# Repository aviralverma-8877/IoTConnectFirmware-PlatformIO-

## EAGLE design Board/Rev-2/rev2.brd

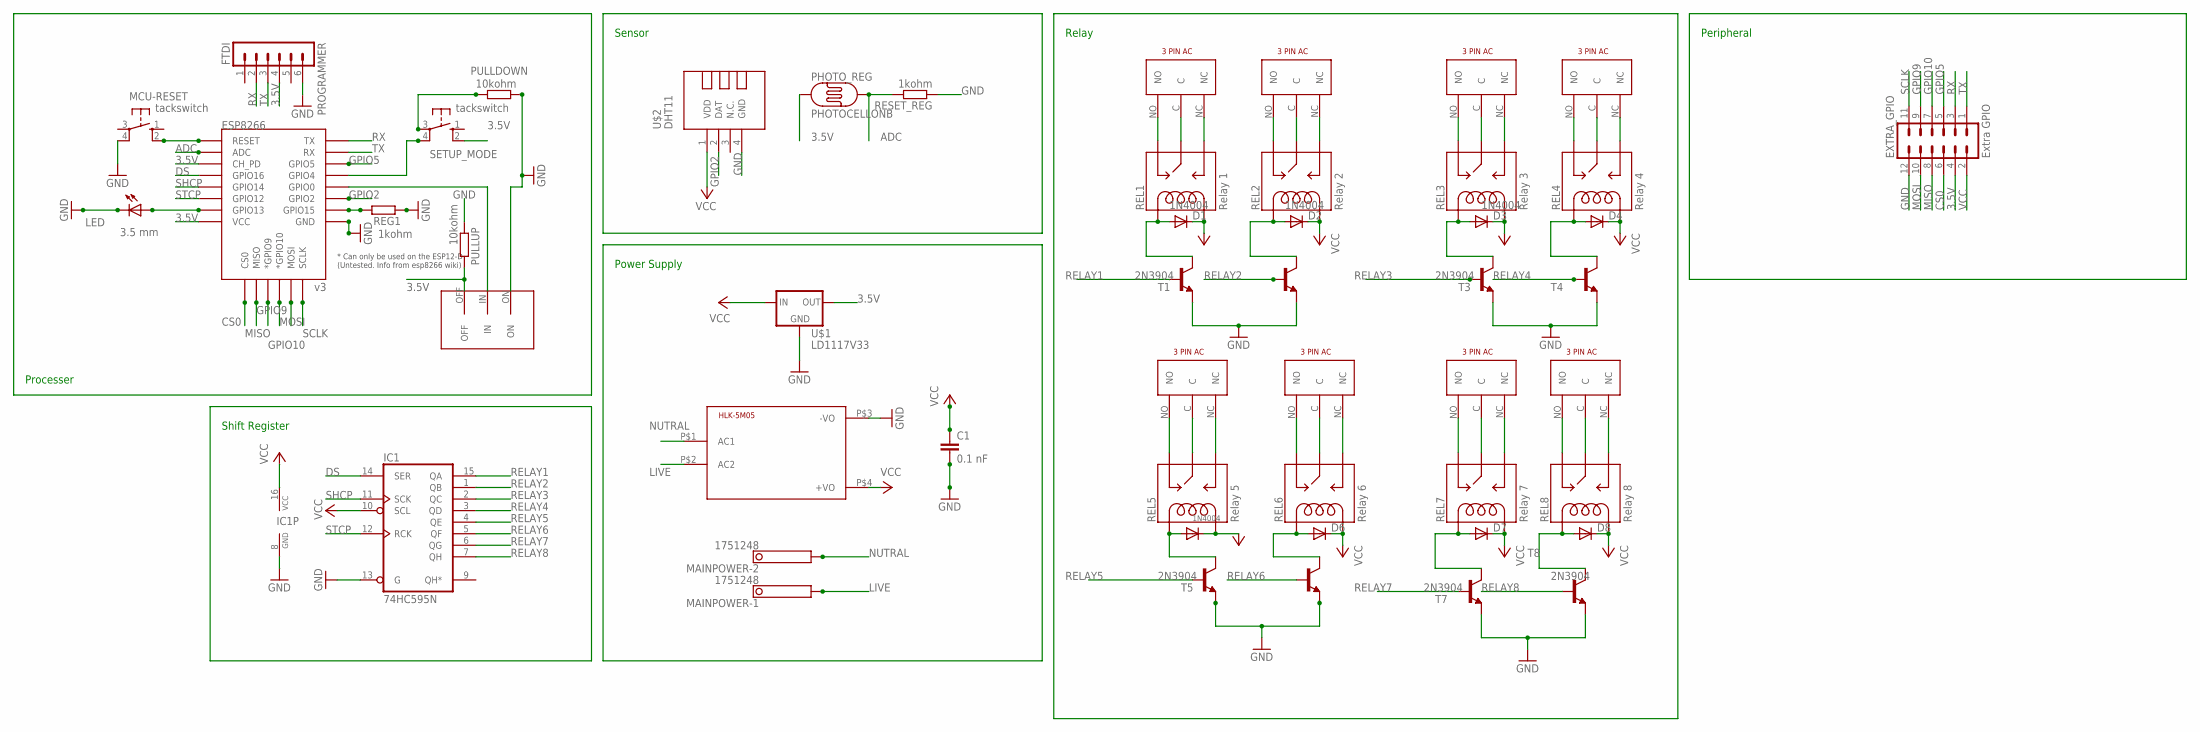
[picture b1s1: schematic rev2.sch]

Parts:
C1: 0.1 nF; CAP-PTH-SMALL-KIT
CON-REL-1, CON-REL-2, CON-REL-3, CON-REL-4, CON-REL-5, CON-REL-6, CON-REL-7, CON-REL-8: 3PINAC; LIB
D1, D2, D3, D4, D5, D6, D7, D8: 1N4004; DO41-10
ESP8266: v3; ESP12E-SMD
EXTRA_GPIO: Extra GPIO; MA06-2
FLASH: TOGGLE_SWITCH
HLK-5M05: AC to DC Converter; HKLPM01
IC1: 74HC595N; DIL16
LED: 3.5 mm; LED3MM
MAINPOWER: 1751248
MCU-RESET: tackswitch; B3F-10XX
PHOTO_REG: PHOTOCELLONB; ON_BOARD
PROGRAMMER: FTDI; MA06-1
PULLDOWN: 10kohm; 0204/7
PULLUP: 10kohm; 0204/7
REG1: 1kohm; 0204/7
REL1: Relay 1; SRD-05VDC-SL-C
REL2: Relay 2; SRD-05VDC-SL-C
REL3: Relay 3; SRD-05VDC-SL-C
REL4: Relay 4; SRD-05VDC-SL-C
REL5: Relay 5; SRD-05VDC-SL-C
REL6: Relay 6; SRD-05VDC-SL-C
REL7: Relay 7; SRD-05VDC-SL-C
REL8: Relay 8; SRD-05VDC-SL-C
RESET_REG: 1kohm; 0204/7
SETUP_MODE: tackswitch; B3F-10XX
T1, T2, T3, T4, T5, T6, T7, T8: 2N3904; TO92-EBC
U$1: LD1117V33
U$2: DHT11; TEMP-HUM-SENSOR-DHT11

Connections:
3.5V: ESP8266.CH_PD, ESP8266.VCC, EXTRA_GPIO.4, FLASH.OFF, PHOTO_REG.1, PROGRAMMER.4, PULLUP.2, SETUP_MODE.2 (S1), U$1.OUT
ADC: ESP8266.ADC, PHOTO_REG.2, RESET_REG.2
CS0: ESP8266.CS0, EXTRA_GPIO.6
DS: ESP8266.GPIO16, IC1.14 (SER)
GND: C1.2, ESP8266.GND, EXTRA_GPIO.12, FLASH.ON, HLK-5M05.P$3 (-VO), IC1.8 (GND), IC1.13 (G), LED.K (C), MCU-RESET.4 (P1), PROGRAMMER.6, PULLDOWN.1, PULLUP.1, REG1.1, RESET_REG.1, T1.E, T2.E, T3.E, T4.E, T5.E, T6.E, T7.E, T8.E, U$1.GND, U$2.4 (GND)
GPIO2: ESP8266.GPIO2, U$2.2 (DAT)
GPIO5: ESP8266.GPIO5, EXTRA_GPIO.5
GPIO9: ESP8266.GPIO9 (*GPIO9), EXTRA_GPIO.9
GPIO10: ESP8266.GPIO10 (*GPIO10), EXTRA_GPIO.7
LIVE: HLK-5M05.P$2 (AC2), MAINPOWER.1
MISO: ESP8266.MISO, EXTRA_GPIO.8
MOSI: ESP8266.MOSI, EXTRA_GPIO.10
unnamed: D5.A, REL5.COIL1, T5.C
unnamed: D6.A, REL6.COIL1, T6.C
unnamed: D7.A, REL7.COIL1, T7.C
unnamed: D8.A, REL8.COIL1, T8.C
unnamed: D4.A, REL4.COIL1, T4.C
unnamed: D3.A, REL3.COIL1, T3.C
unnamed: ESP8266.GPIO13, LED.A
unnamed: D2.A, REL2.COIL1, T2.C
unnamed: D1.A, REL1.COIL1, T1.C
unnamed: CON-REL-5.NC, REL5.SWOPEN
unnamed: CON-REL-5.C, REL5.SWCOMMON
unnamed: CON-REL-5.NO, REL5.SWCLOSED (SWCLOSE)
unnamed: CON-REL-6.NC, REL6.SWOPEN
unnamed: CON-REL-6.C, REL6.SWCOMMON
unnamed: CON-REL-6.NO, REL6.SWCLOSED (SWCLOSE)
unnamed: CON-REL-7.NC, REL7.SWOPEN
unnamed: CON-REL-7.C, REL7.SWCOMMON
unnamed: CON-REL-7.NO, REL7.SWCLOSED (SWCLOSE)
unnamed: CON-REL-8.NC, REL8.SWOPEN
unnamed: CON-REL-8.C, REL8.SWCOMMON
unnamed: CON-REL-8.NO, REL8.SWCLOSED (SWCLOSE)
unnamed: CON-REL-4.NC, REL4.SWOPEN
unnamed: CON-REL-4.C, REL4.SWCOMMON
unnamed: CON-REL-4.NO, REL4.SWCLOSED (SWCLOSE)
unnamed: CON-REL-3.NC, REL3.SWOPEN
unnamed: ESP8266.GPIO4, SETUP_MODE.4 (P1)
unnamed: ESP8266.GPIO15, REG1.2
unnamed: ESP8266.GPIO0, FLASH.IN
unnamed: PULLDOWN.2, SETUP_MODE.3
unnamed: ESP8266.RESET, MCU-RESET.2 (S1)
unnamed: CON-REL-3.C, REL3.SWCOMMON
unnamed: CON-REL-3.NO, REL3.SWCLOSED (SWCLOSE)
unnamed: CON-REL-2.NC, REL2.SWOPEN
unnamed: CON-REL-2.C, REL2.SWCOMMON
unnamed: CON-REL-2.NO, REL2.SWCLOSED (SWCLOSE)
unnamed: CON-REL-1.NC, REL1.SWOPEN
unnamed: CON-REL-1.C, REL1.SWCOMMON
unnamed: CON-REL-1.NO, REL1.SWCLOSED (SWCLOSE)
NUTRAL: HLK-5M05.P$1 (AC1), MAINPOWER.2
RELAY1: IC1.15 (QA), T1.B
RELAY2: IC1.1 (QB), T2.B
RELAY3: IC1.2 (QC), T3.B
RELAY4: IC1.3 (QD), T4.B
RELAY5: IC1.4 (QE), T5.B
RELAY6: IC1.5 (QF), T6.B
RELAY7: IC1.6 (QG), T7.B
RELAY8: IC1.7 (QH), T8.B
RX: ESP8266.TXD0 (TX), EXTRA_GPIO.3, PROGRAMMER.2
SCLK: ESP8266.SCLK, EXTRA_GPIO.11
SHCP: ESP8266.GPIO14, IC1.11 (SCK)
STCP: ESP8266.GPIO12, IC1.12 (RCK)
TX: ESP8266.RXD0 (RX), EXTRA_GPIO.1, PROGRAMMER.3
VCC: C1.1, D1.C, D2.C, D3.C, D4.C, D5.C, D6.C, D7.C, D8.C, EXTRA_GPIO.2, HLK-5M05.P$4 (+VO), IC1.10 (SCL), IC1.16 (VCC), REL1.COIL0, REL2.COIL0, REL3.COIL0, REL4.COIL0, REL5.COIL0, REL6.COIL0, REL7.COIL0, REL8.COIL0, U$1.IN, U$2.1 (VDD)

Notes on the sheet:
Processer
Shift Register
Power Supply
Sensor
Relay
Peripheral

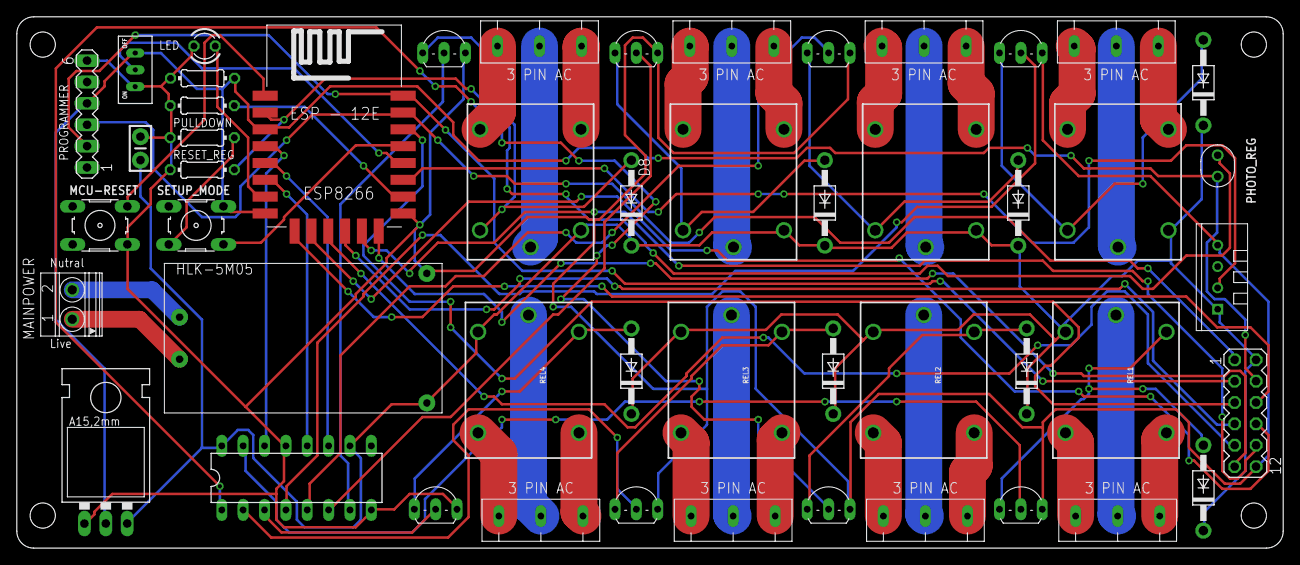
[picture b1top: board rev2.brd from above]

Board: 2 copper layers, 150.6 x 63.2 mm, 50 parts (0 on the bottom side), 65 nets.

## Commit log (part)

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2019-02-20 IoT Connect Platform IO Firmware
2019-02-20 Fetch IP Fix
2019-02-20 ssl to mqtt added
2019-06-14 JSON Library updated
2019-10-10 IP Fix
2020-04-28 Lib added
2020-04-28 EEPROM Handling
2020-06-17 pinging time added
2020-06-19 RSSI added
2020-06-30 Local Ip Added
2020-07-01 Webserver Added
2020-07-01 Web Server Support
2020-07-01 Local Web Server
2020-07-01 Web Server Updates
2020-07-02 Web server update
2020-07-07 CAP arduino code added
2020-07-07 serial fix
2020-07-11 Hostname support added
2020-07-15 Board Files added
2020-07-16 Board Generated
2020-07-22 Time out increased
2020-07-23 SPIFFS Support Added
2020-07-23 Temp + Humid + Lumin Support
2020-07-23 board updated
2020-07-26 Online WiFi Update added
2020-07-26 UI change
2020-07-28 LED Fix
2020-07-30 Reconnect option added
2020-07-31 On board led control added
2020-08-02 Async meathod added
2020-08-02 Async Updates and Fixes
2020-08-03 Fixes
2020-08-07 Auth added
2020-08-09 Multiple files
2020-08-09 Error Fix
2020-08-09 Filesystem error removed
2020-08-09 Fix branch
2020-08-09 Revert "Fixes"
    This reverts commit de97f7f5cf6718cf6572ba5a8cc5142759cc83c7.
2020-08-09 Web Sockets Added
2020-08-09 Color Code Added
2020-08-09 define values fix
2020-08-09 toggle switch added
2020-08-09 reset fix
2020-08-10 obl function fix
2020-08-15 Device Config Added
2020-08-16 MQTT Topic Generation
2020-08-17 MQTT Subs
2020-08-17 MQTT Refactoring
2020-08-18 MQTT Sync
2020-08-18 Device Config
2020-08-18 Status update
2020-08-21 MQTT Config
2020-08-21 MQTT Action
2020-08-22 Socket FIx
2020-08-23 mqtt complete
2020-08-23 SPIFFS refactored
2020-08-26 Reset Button Function added
2020-08-26 Gobal -> Local
2020-08-26 Flows added
2020-08-26 refactoring
2020-09-01 SPIFFS updated
2020-09-02 eeprom Save option
2020-09-02 Save to EEPROM Completed
2020-09-02 MQTT Error Fix
2020-09-02 MQTT Fix
2020-09-02 Config Reset Fix
2020-09-03 MQTT Connect fix
2020-09-04 MQTTStatus Fix
2020-09-04 BTN fix
2020-09-04 UI fix
2020-09-04 Relay btn action
2020-09-05 DHT fix
2020-09-05 CHIPID added
2020-09-06 minified
2020-09-06 Security added
2020-09-07 WiFi Fix
2020-09-08 Fauxmo Support added
2020-09-09 fauxmo Fix
2020-09-09 Reload added
2020-09-10 WiFi Connect Fix
2020-09-18 Hostname Fix
2020-10-02 Topic added to UI
2020-10-02 MQTT Topic added to UI
2020-10-18 Board file updated
2020-10-20 Websocket Fix
2020-10-21 Latest Firmware URL added
2020-10-30 DNS Address Added
2020-11-09 Pairing Added
2020-11-09 Buttons added
2021-03-17 Eagle Design Updated
2021-05-11 Board Update
2021-05-11 Update Screen
2021-05-18 Reactivate MQTT Added
2021-05-21 WiFi Disconnect Fix
2021-05-21 WiFi MQTT Disconnect/Reconnect fix
2021-05-22 WiFi/MQTT Fix
2021-05-22 UI Update
2021-05-22 Revert "UI Update"
    This reverts commit 852503a3ec7038c0f35cb9643a175808699e7ba4.
2021-05-22 MQTT Server Updated
2021-05-30 subscribed_to_mqtt_topics removed
2021-05-31 FetchIp Fix
2021-06-09 Sensor Fix
2021-06-12 QOS switched to 2
2021-06-14 Fouxmo Fix
2021-06-14 Library Updated and fauxmo Fix
2021-06-15 Sensor Data Fix
2021-06-17 dns fix
2021-06-17 version Upgraded to 2.1.9
2021-06-18 lib include placement
2021-06-22 MQTT QoS Added
2021-06-29 esp01 to esp01_1m
2021-07-06 platform io update
2021-08-07 Long Prefix Fix
2021-08-07 platform.ini update
2021-08-10 Version Upgraded
2021-08-18 UI Changes
2021-08-18 pcb design update
2021-08-18 Board Updates
2021-08-19 Rev 3 Added
2021-08-20 MQTT Data Display
2021-08-20 Timeout Added
2021-08-20 Web UI Fix
2021-08-21 Relay Toggle Fix
2021-08-23 Web Socket Fix
2021-08-27 Free heap Fix
2021-08-28 Reboot Error Fix
2021-09-04 WiFi Signal strength added to ssid scan
2021-09-04 Template set from WebSocket to WebServer
2021-09-04 Captive portal enabled
2021-09-05 Custom Alert
2021-09-05 button styling
2021-09-05 button layout fix
2021-09-05 UI Fixes
2021-09-07 Mods for ESP32
2021-09-07 ESP32 changes
2021-09-12 WiFi Scan Fix
2021-09-13 Sockets initilized before webserver
2021-09-13 Priority
2021-09-14 Generate Mqtt Topic Fix
2021-09-15 Ticke fix
2021-09-16 revert
2021-09-17 Websocket Connection fix
2021-11-02 Local MQTT Fix
2021-12-02 Fauxmo device miss match handled
2021-12-02 Foxmo Fix
2021-12-14 Font fix
2021-12-14 Cganged to 8 device discovery
2021-12-14 Debugging removed
2021-12-14 Reset Button Fix
2021-12-14 Remove device fix
2021-12-15 Alexa 8 Relay Control Enabled
2021-12-22 BLE Supoort Added WIP
2021-12-22 BLE added
2022-06-06 Indentation fix
2022-06-06 Sensor meathods seperated out
2022-06-06 Sensor files seperated.
2022-08-30 Jenkins File added
2022-08-30 all env added to Jenkins File
2022-08-30 clean step added
2022-08-30 Create Output
2023-10-18 For loop fix
2023-10-18 Keyword fix
2023-10-20 2.2.4 fix
2023-10-20 Moved to old arduino framework
2024-03-15 Gitignore updated
2024-03-15 git ignore updated
2024-04-17 New Arduino JSON opted.
2024-06-03 Version updated.
2025-04-18 Platform.ini updated
2025-04-20 bugfix
2025-10-21 Wifi ap fix
2025-10-21 Warning fixes
2025-11-01 Littlefs update

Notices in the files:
parts and their libraries:
SparkFun-Capacitors: Licensing: Creative Commons ShareAlike 4.0 International - https://creativecommons.org/licenses/by-sa/4.0
diy-modules: Released under the Creative Commons Attribution 4.0 International License: http://creativecommons.org/licenses/by/4.0
